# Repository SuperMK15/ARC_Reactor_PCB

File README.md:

# Arc Reactor PCB

Wi-Fi controllable arc reactor board featuring an **ESP32-C3-MINI-1**, native USB flashing, a dual-diode power OR-ing circuit, and a 9-LED WS2812B addressable ring. Powered by a 2S–4S battery or USB-C.

## Features

- ESP32-C3-MINI-1 module with onboard Wi-Fi
- 9x WS2812B-B/W addressable RGB LEDs in a center-and-ring layout
- Native USB-C interface for data flashing and 5V power input
- Dual-diode power OR-ing circuit (LM66200) for seamless switching between USB and battery power
- Wide-input synchronous step-down buck converter (AP63205) supporting 2S–4S LiPo inputs
- Low-dropout regulator (AP2112K-3.3) for stable 3.3V MCU power
- SN74AHCT1G125 level shifter for reliable 3.3V to 5V WS2812B data transmission
- TVS diode (SMAJ18A) and breakout header for UART serial debugging

## PCB Layers

### Front Copper

### Internal Ground (In1)

### Internal Power (In2)

### Back Copper

## Design Files

Designed in **KiCad 10**. Includes the complete schematic, 4-layer PCB layout, Bill of Materials (BOM), Component Placement List (CPL), and fabrication files.

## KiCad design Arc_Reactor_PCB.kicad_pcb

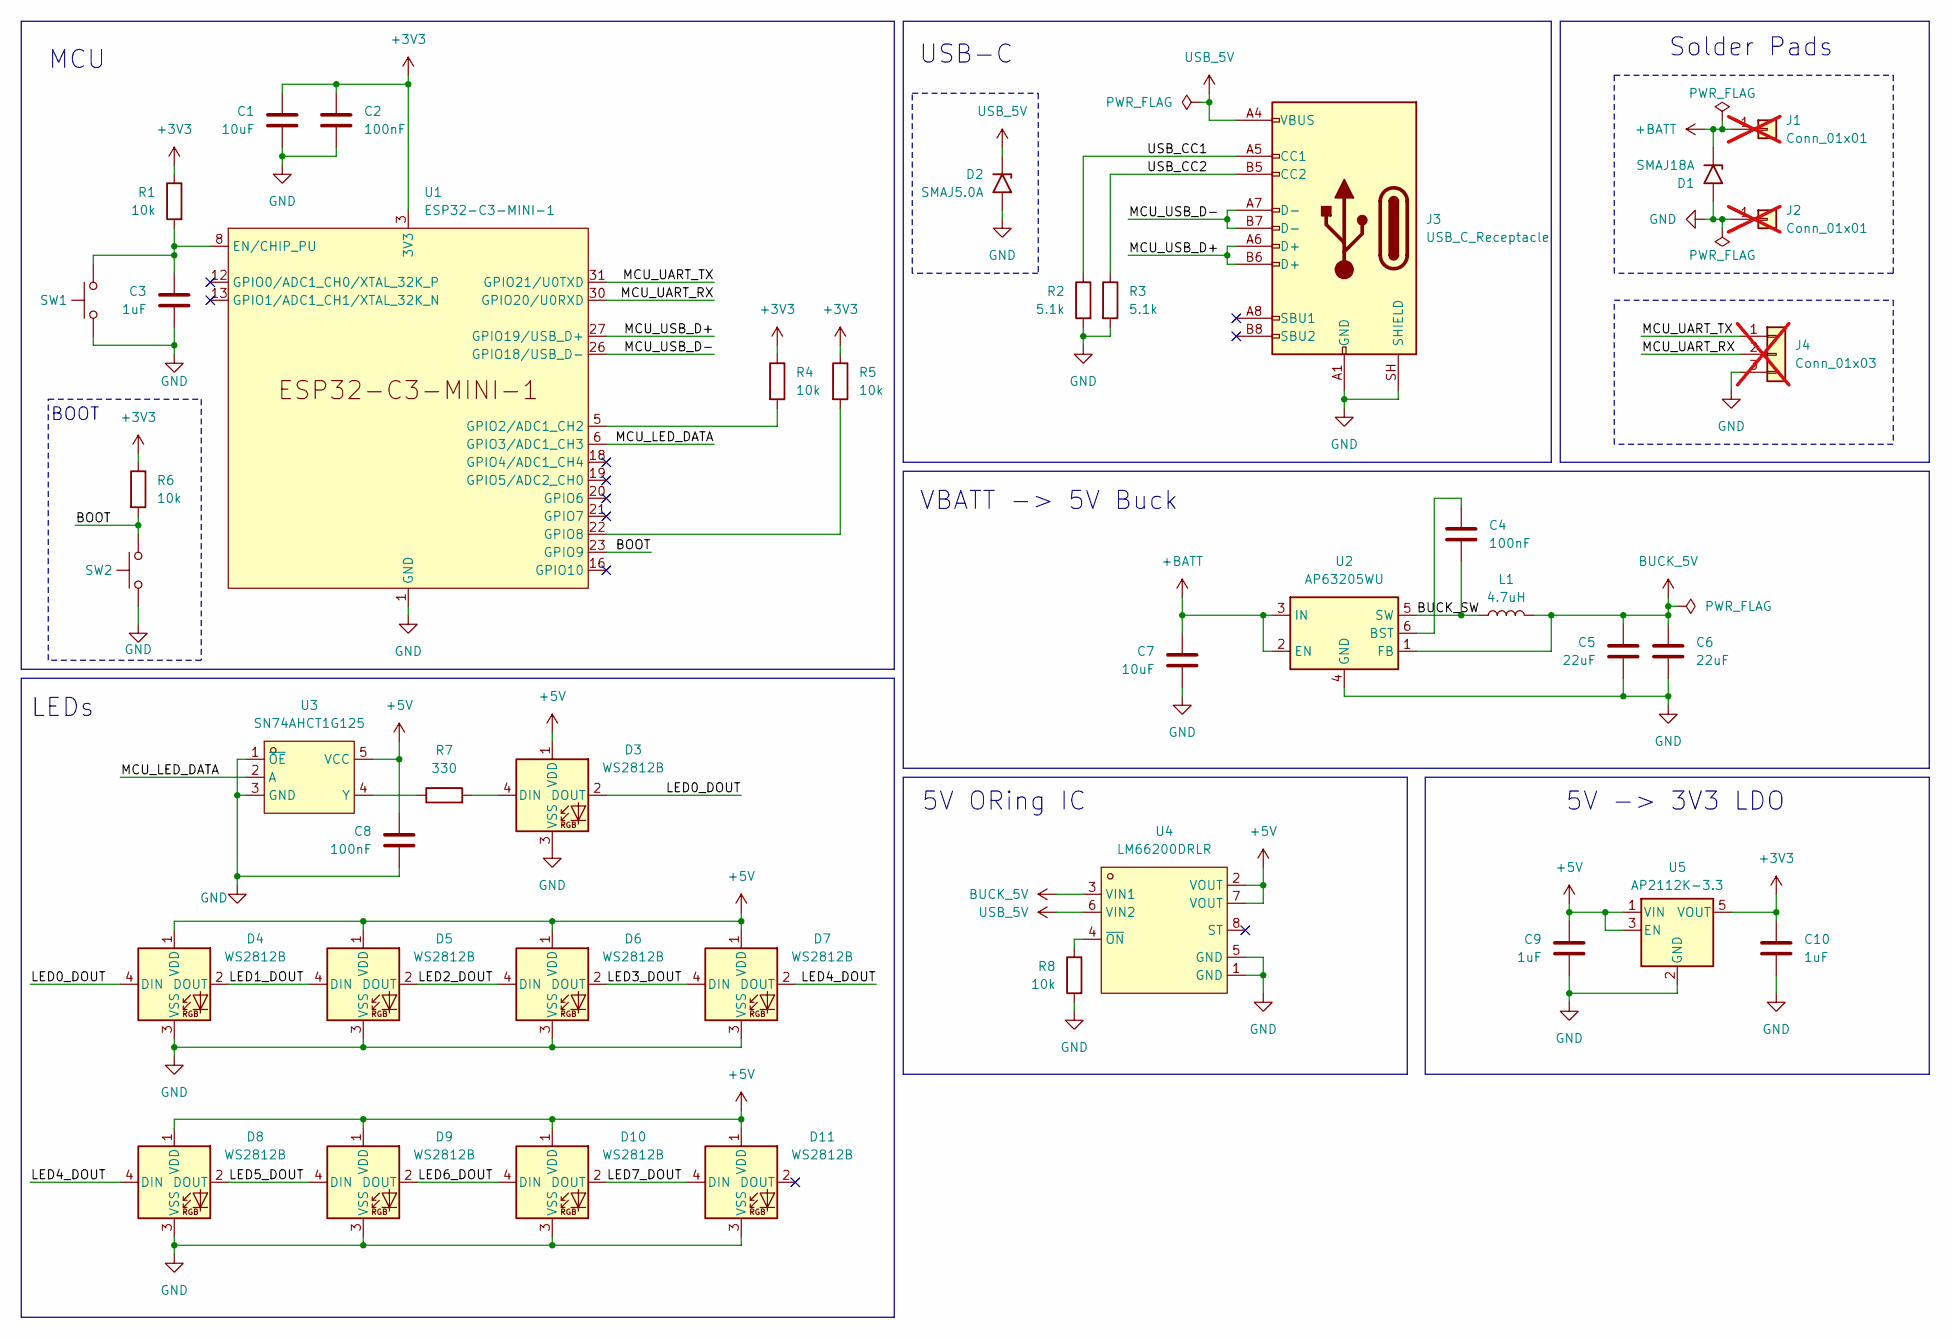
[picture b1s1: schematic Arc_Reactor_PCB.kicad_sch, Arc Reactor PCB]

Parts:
C1: 10uF; C_0603_1608Metric; LCSC C19702
C2, C4, C8: 100nF; C_0603_1608Metric; LCSC C14663
C3, C9, C10: 1uF; C_0603_1608Metric; LCSC C90540
C5, C6: 22uF; C_0805_2012Metric; LCSC C45783
C7: 10uF; C_0805_2012Metric; LCSC C318691
D1: SMAJ18A; D_SMA; LCSC C134965
D2: SMAJ5.0A; D_SMA; LCSC C83329
D3, D4, D5, D6, D7, D8, D9, D10, D11: WS2812B; LED_WS2812B_PLCC4_5.0x5.0mm_P3.2mm; LCSC C114586
J1, J2: Conn_01x01; SolderWire-0.5sqmm_1x01_D0.9mm_OD2.3mm; not fitted
J3: USB_C_Receptacle; USB_C_Receptacle_HRO_TYPE-C-31-M-12; LCSC C2765186
J4: Conn_01x03; PinHeader_1x03_P2.54mm_Vertical; not fitted
L1: 4.7uH; IND-SMD_L4.0-W4.0_FNR40XXS; LCSC C167874
R1, R4, R5, R6, R8: 10k; R_0603_1608Metric; LCSC C98220
R2, R3: 5.1k; R_0603_1608Metric; LCSC C23186
R7: 330; R_0603_1608Metric; LCSC C23138
SW1, SW2: SW_Push; SW_SPST_TS-1088-xR020; LCSC C720477
U1: ESP32-C3-MINI-1; LCSC C2838502
U2: AP63205WU; TSOT-23-6; LCSC C2071056
U3: SN74AHCT1G125; SOT-23-5_L3.0-W1.7-P0.95-LS2.8-BR; LCSC Part C7484
U4: LM66200DRLR; SOT-583-8_L2.1-W1.2-P0.50-LS1.6-BL; LCSC Part C3235556
U5: AP2112K-3.3; SOT-23-5; LCSC C51118

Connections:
+3V3: C1.2, C2.2, C10.2, R1.1, R4.1, R5.1, R6.1, U1.3 (3V3), U5.5 (VOUT)
+5V: C8.2, C9.2, D3.1 (VDD), D4.1 (VDD), D5.1 (VDD), D6.1 (VDD), D7.1 (VDD), D8.1 (VDD), D9.1 (VDD), D10.1 (VDD), D11.1 (VDD), U3.5 (VCC), U4.2 (VOUT), U4.7 (VOUT), U5.1 (VIN), U5.3 (EN)
+BATT: C7.2, D1.1 (A1), J1.1 (Pin_1_1), U2.2 (EN), U2.3 (IN)
/BOOT: R6.2, SW2.2, U1.23 (GPIO9)
/BUCK_SW: C4.1, L1.1, U2.5 (SW)
/LED0_DOUT: D3.2 (DOUT), D4.4 (DIN)
/LED1_DOUT: D4.2 (DOUT), D5.4 (DIN)
/LED2_DOUT: D5.2 (DOUT), D6.4 (DIN)
/LED3_DOUT: D6.2 (DOUT), D7.4 (DIN)
/LED4_DOUT: D7.2 (DOUT), D8.4 (DIN)
/LED5_DOUT: D8.2 (DOUT), D9.4 (DIN)
/LED6_DOUT: D9.2 (DOUT), D10.4 (DIN)
/LED7_DOUT: D10.2 (DOUT), D11.4 (DIN)
/MCU_LED_DATA: U1.6 (GPIO3/ADC1_CH3), U3.2 (A)
/MCU_UART_RX: J4.2, U1.30 (GPIO20/U0RXD)
/MCU_UART_TX: J4.1, U1.31 (GPIO21/U0TXD)
/MCU_USB_D+: J3.A6 (D+), J3.B6 (D+), U1.27 (GPIO19/USB_D+)
/MCU_USB_D-: J3.A7 (D-), J3.B7 (D-), U1.26 (GPIO18/USB_D-)
/USB_CC1: J3.A5 (CC1), R2.1
/USB_CC2: J3.B5 (CC2), R3.1
BUCK_5V: C5.2, C6.2, L1.2, U2.1 (FB), U4.3 (VIN1)
GND: C1.1, C2.1, C3.1, C5.1, C6.1, C7.1, C8.1, C9.1, C10.1, D1.2 (A2), D2.2 (A2), D3.3 (VSS), D4.3 (VSS), D5.3 (VSS), D6.3 (VSS), D7.3 (VSS), D8.3 (VSS), D9.3 (VSS), D10.3 (VSS), D11.3 (VSS), J2.1 (Pin_1_1), J3.A1 (GND), J3.A12 (GND), J3.B1 (GND), J3.B12 (GND), J3.SH (SHIELD), J4.3, R2.2, R3.2, R8.2, SW1.1, SW2.1, U1.1 (GND), U1.2 (GND), U1.11 (GND), U1.14 (GND), U1.36 (GND), U1.37 (GND), U1.38 (GND), U1.39 (GND), U1.40 (GND), U1.41 (GND), U1.42 (GND), U1.43 (GND), U1.44 (GND), U1.45 (GND), U1.46 (GND), U1.47 (GND), U1.48 (GND), U1.49 (GND), U1.50 (GND), U1.51 (GND), U1.52 (GND), U1.53 (GND), U2.4 (GND), U3.1 (~OE), U3.3 (GND), U4.1 (GND), U4.5 (GND), U5.2 (GND)
unnamed: D3.4 (DIN), R7.2
unnamed: C3.2, R1.2, SW1.2, U1.8 (EN/CHIP_PU)
unnamed: R4.2, U1.5 (GPIO2/ADC1_CH2)
unnamed: R5.2, U1.22 (GPIO8)
unnamed: C4.2, U2.6 (BST)
unnamed: R7.1, U3.4 (Y)
unnamed: R8.1, U4.4 (~ON)
USB_5V: D2.1 (A1), J3.A4 (VBUS), J3.A9 (VBUS), J3.B4 (VBUS), J3.B9 (VBUS), U4.6 (VIN2)

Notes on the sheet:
MCU
BOOT
USB-C
Solder Pads
VBATT -> 5V Buck
5V -> 3V3 LDO
LEDs
5V ORing IC

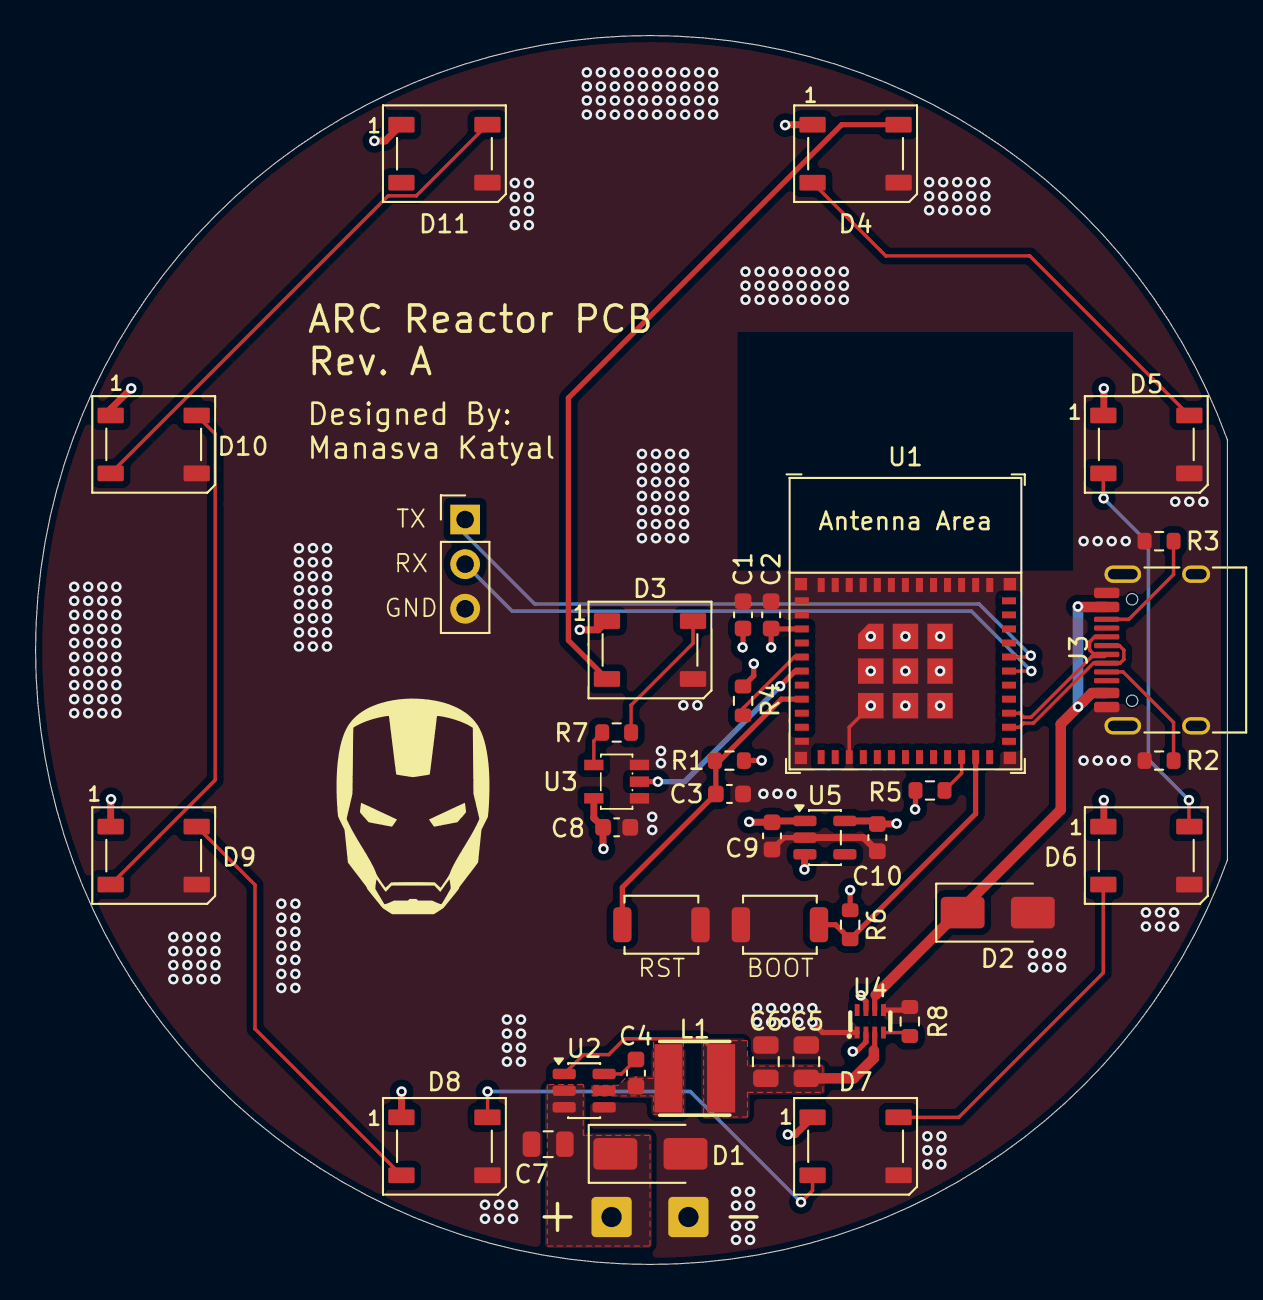
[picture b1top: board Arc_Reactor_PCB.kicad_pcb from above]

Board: 4 copper layers, 67.9 x 70.0 mm, 43 parts (1 on the bottom side), 30 nets.

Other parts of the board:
G1, G2: LOGO
